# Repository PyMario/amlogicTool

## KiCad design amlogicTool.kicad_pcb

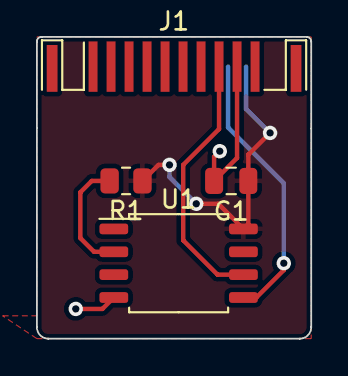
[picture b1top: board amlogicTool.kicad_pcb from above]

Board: 2 copper layers, 15.2 x 16.8 mm, 4 parts (0 on the bottom side), 5 nets.

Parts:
C?: C; C_0805_2012Metric
J1: HDMI_A; HDMI_A_Contact_Technology_HDMI-19APL2_Horizontal
R?: R; R_0805_2012Metric
U?: AT24CS01-MAHM; SOP-8_5.28x5.23mm_P1.27mm

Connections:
/SCL: J1.15 (SCL), U?.6 (SCL)
/SDA: J1.16 (SDA), U?.5 (SDA)
GND: C?.2, J1.17 (GND), U?.4 (GND)
unnamed: R?.2, U?.2 (A1)
VCC: C?.1, J1.18 (+5V), R?.1, U?.8 (VCC)
